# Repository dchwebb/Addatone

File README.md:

# Addatone

Overview
--------

Addatone is a Eurorack oscillator using additive synthesis. It is a two channel oscillator with channel one outputting fundamental and odd harmonics and channel two fundamental and even harmonics.

Each channel has potentiometer and CV control over the number of harmonics with higher harmonics progressively attenuated. In addition a 'Count' pot and CV input hard-limit the total number of audible harmonics. A warp control progressively detunes the odd harmonics up and even harmonics down.

Channel one has a mix switch which allows a mix of both channels to be output from channel one. Channel two has a multiply switch which allows a multiple of both channels to be output from channel two (ie a ring modulation effect).

The final controls are an octave potentiometer covering a five octave range and a fine tune control covering around an octave.

Architecture
------------

The core sound generator is an ICE40UP5K FPGA from Lattice. This is responsible for generating the harmonics, mixing/multiplying and then outputting to the DAC via I2S protocol.

The module also contains an STM32F446 microcontroller which holds the FPGA bitstream in internal flash memory; this is used to program the FPGA on start-up via SPI. In addition the STM32 is used as an ADC to digitise and scale all potentiometer and CV control data. This is periodically transferred to the FPGA via SPI. The STM32 is clocked from an external 12MHz crystal. This is also used to drive the FPGA clock via the STM32 MCO (Master Clock Output) peripheral.

The DAC is a Texas Instruments PCM5100APW, operating 2 channels at 16 bits, 48kHz. Two op-amps are used to scale input CV voltages and to amplify the DAC output to Eurorack levels (8V peak to peak).

FPGA
----

A look-up table in block RAM (Sine_LUT) holds 2048 16 bit samples containing a single cycle sine wave. Individual harmonics are generated by traversing the LUT at a speed relative to the harmonic frequency.

The SamplePos_RAM 256 x 16 bit look-up table holds the current Sine LUT position of each harmonic. This position is advanced according to the harmonic's frequency at each sample and the sine sample is scaled and added to an accumulator. The initial values of the sample position LUT are pre-calculated to minimise 'crest factor'. If each harmonic started at position 0 of a sine wave then peaks and troughs would coincide to create a wave with an amplitude greater than the dynamic range of the system.

A graphical javascript tool to visualise and calculate minimal crest factor sample positions is available here:
https://htmlpreview.github.io/?https://raw.githubusercontent.com/dchwebb/Addatone/master/SamplePosLUT/SineLUT.htm

The FPGA receives its control data from the ADCs processed in the STM32. These are periodically sent via SPI and decoded using a custom peripheral (ADC_SPI_In).

The DAC_I2S module is a custom peripheral used to dispatch the final sample values to the DAC via the I2S protocol.

The 12MHz clock received from the STM32 MCO is scaled to the ICE40's maximum clock frequency of 48MHz.

The ICE40 bitstream is developed in Lattice's Radiant IDE. Full source code here: https://github.com/dchwebb/Addatone/tree/master/Addatone_ICE40

STM32 Microcontroller
---------------------

The module includes an STM32F446 MCU that carries out various helper roles. The firmware was developed in STM's CubeIDE and available here: https://github.com/dchwebb/Addatone/tree/master/Addatone_STM32F446

The FPGA bitstream is stored in the MCU's flash memory and is programmed into the FPGA at startup using an STM32 SPI peripheral (see fpgaHandler::ProgramBitstream method). Once the FPGA is programmed the ADC data derived from external CV control and potentiometers is processed, scaled and transmitted in a periodic packet to the FPGA via SPI (see fpgaHandler::SendControls method).

Calibration
-----------

The 'calib' button allows the setting of the mid point of the fine tune and the spread of the tuning. To start calibration turn the Octave and Fine Tune knobs to their mid point position.

Press the Calib button. Changing the Fine Tune knob will alter the pitch. Turning the Octave knob clockwise will decrease the tuning spread, and vice versa.

When calibration is complete press the Calib button again. Turning the Fine Tune knob to the center position should set the correct pitch.

To erase the configured calibration hold the Calib button down when powering on the module.

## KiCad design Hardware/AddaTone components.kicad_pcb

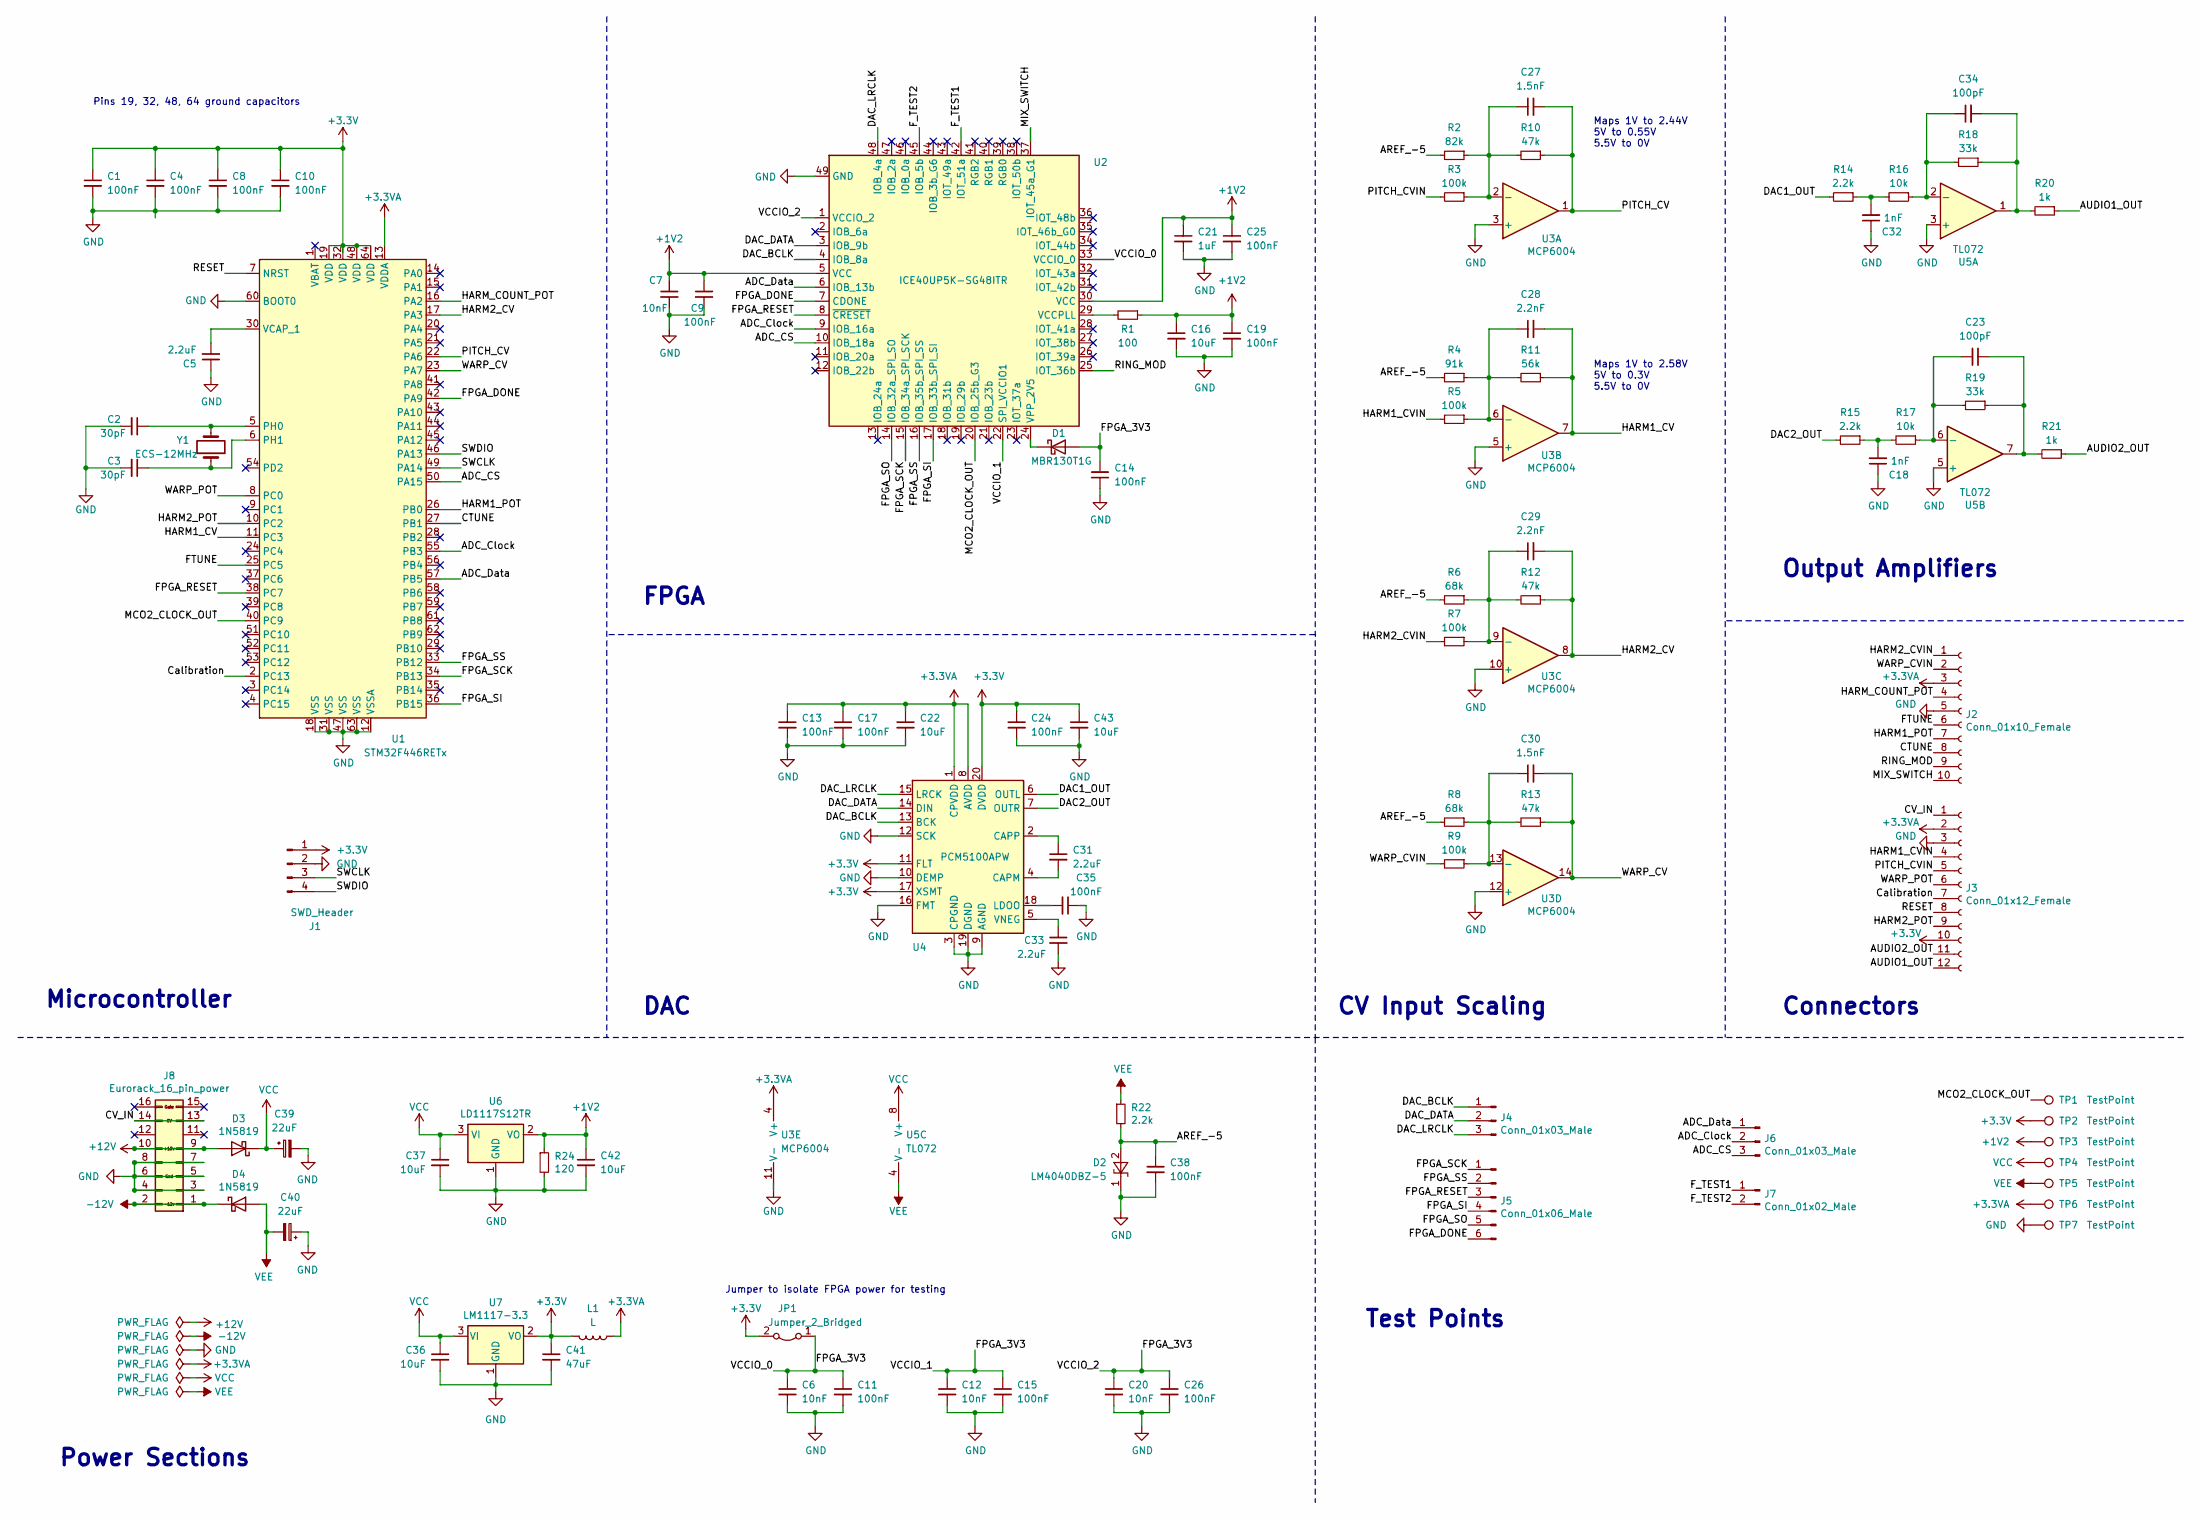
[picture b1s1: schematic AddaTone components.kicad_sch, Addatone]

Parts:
C1, C4, C9, C15, C35: 100nF; C_0603_1608Metric_Pad1.08x0.95mm_HandSolder
C2, C3: 30pF; C_0805_2012Metric_Pad1.18x1.45mm_HandSolder
C5, C31, C33: 2.2uF; C_0805_2012Metric_Pad1.18x1.45mm_HandSolder
C6, C7, C12, C20: 10nF; C_0805_2012Metric_Pad1.18x1.45mm_HandSolder
C8, C10, C11, C13, C14, C17, C19, C24, C25, C26, C38: 100nF; C_0805_2012Metric_Pad1.18x1.45mm_HandSolder
C16, C22, C43: 10uF; C_0805_2012Metric_Pad1.18x1.45mm_HandSolder
C18, C32: 1nF; C_0805_2012Metric_Pad1.18x1.45mm_HandSolder
C21: 1uF; C_0805_2012Metric_Pad1.18x1.45mm_HandSolder
C23, C34: 100pF; C_0805_2012Metric_Pad1.18x1.45mm_HandSolder
C27, C30: 1.5nF; C_0805_2012Metric_Pad1.18x1.45mm_HandSolder
C28, C29: 2.2nF; C_0805_2012Metric_Pad1.18x1.45mm_HandSolder
C36, C37, C42: 10uF; CP_Elec_3x5.3
C39, C40: 22uF; CP_Elec_5x5.3
C41: 47uF; CP_Elec_5x5.3
D1: MBR130T1G; D_SOD-123
D2: LM4040DBZ-5; SOT-23
D3, D4: 1N5819; D_SOD-123
J1: SWD_Header; SWD_header
J2: Conn_01x10_Female; PinSocket_1x10_P2.54mm_Vertical
J3: Conn_01x12_Female; PinSocket_1x12_P2.54mm_Vertical
J4, J6: Conn_01x03_Male; PinHeader_1x03_P2.54mm_Vertical
J5: Conn_01x06_Male; PinHeader_2x03_P2.54mm_Vertical
J7: Conn_01x02_Male; PinHeader_1x02_P2.54mm_Vertical
J8: Eurorack_16_pin_power; Eurorack_16_pin_header
JP1: Jumper_2_Bridged; SolderJumper-2_P1.3mm_Bridged_Pad1.0x1.5mm
L1: L; L_0805_2012Metric_Pad1.15x1.40mm_HandSolder
R1: 100; R_0805_2012Metric_Pad1.20x1.40mm_HandSolder
R2: 82k; R_0805_2012Metric_Pad1.20x1.40mm_HandSolder
R3, R5, R7, R9: 100k; R_0805_2012Metric_Pad1.20x1.40mm_HandSolder
R4: 91k; R_0805_2012Metric_Pad1.20x1.40mm_HandSolder
R6, R8: 68k; R_0805_2012Metric_Pad1.20x1.40mm_HandSolder
R10, R12, R13: 47k; R_0805_2012Metric_Pad1.20x1.40mm_HandSolder
R11: 56k; R_0805_2012Metric_Pad1.20x1.40mm_HandSolder
R14, R15, R22: 2.2k; R_0805_2012Metric_Pad1.20x1.40mm_HandSolder
R16, R17: 10k; R_0805_2012Metric_Pad1.20x1.40mm_HandSolder
R18, R19: 33k; R_0805_2012Metric_Pad1.20x1.40mm_HandSolder
R20, R21: 1k; R_0805_2012Metric_Pad1.20x1.40mm_HandSolder
R24: 120; R_0805_2012Metric_Pad1.20x1.40mm_HandSolder
TP1, TP2, TP3, TP4, TP5, TP6, TP7: TestPoint; TestPoint_THTPad_2.0x2.0mm_Drill1.0mm
U1: STM32F446RETx; LQFP-64_10x10mm_P0.5mm
U2: ICE40UP5K-SG48ITR; ICE40_QFN-48-1EP_7x7mm_Pitch0.5mm
U3: MCP6004; SOIC-14_3.9x8.7mm_P1.27mm
U4: PCM5100APW; SSOP-20_4.4x6.5mm_Pitch0.65mm_Round_Pads
U5: TL072; SOIC-8_3.9x4.9mm_P1.27mm
U6: LD1117S12TR; SOT-223
U7: LM1117-3.3; SOT-223
Y1: ECS-12MHz; Crystal_SMD_0603-2pin_6.0x3.5mm_HandSoldering

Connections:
+1V2: C7.1, C9.1, C16.1, C19.1, C21.1, C25.1, C42.1, R1.1, R24.1, TP3.1, U2.5 (VCC), U2.30 (VCC), U6.2 (VO)
+3.3VA: C13.1, C17.1, C22.1, J2.3, J3.2, L1.1, TP6.1, U1.13 (VDDA), U3.4 (V+), U4.1 (CPVDD), U4.8 (AVDD)
+3V3: C1.1, C4.1, C8.1, C10.1, C24.1, C41.1, C43.1, J1.1, J3.10, JP1.2 (B), L1.2, TP2.1, U1.19 (VDD), U1.32 (VDD), U1.48 (VDD), U1.64 (VDD), U4.11 (FLT), U4.17 (XSMT), U4.20 (DVDD), U7.2 (VO)
+12V: D3.2 (A), J8.9, J8.10
-12V: D4.1 (K), J8.1, J8.2
/ADC_CS: J6.3, U1.50 (PA15), U2.10 (IOB_18a)
/ADC_Clock: J6.2, U1.55 (PB3), U2.9 (IOB_16a)
/ADC_Data: J6.1, U1.57 (PB5), U2.6 (IOB_13b)
/AREF_-5: C38.1, D2.2 (A), R2.2, R4.2, R6.2, R8.2, R22.2
/AUDIO1_OUT: J3.12, R20.1
/AUDIO2_OUT: J3.11, R21.1
/CTUNE: J2.8, U1.27 (PB1)
/CV_IN: J3.1, J8.13, J8.14
/Calibration: J3.7, U1.2 (PC13)
/DAC1_OUT: R14.2, U4.6 (OUTL)
/DAC2_OUT: R15.2, U4.7 (OUTR)
/DAC_BCLK: J4.1, U2.4 (IOB_8a), U4.13 (BCK)
/DAC_DATA: J4.2, U2.3 (IOB_9b), U4.14 (DIN)
/DAC_LRCLK: J4.3, U2.48 (IOB_4a), U4.15 (LRCK)
/FPGA_3V3: C6.1, C11.1, C12.1, C14.2, C15.1, C20.1, C26.1, D1.2 (A), JP1.1 (A), U2.1 (VCCIO_2), U2.22 (SPI_VCCIO1), U2.33 (VCCIO_0)
/FPGA_DONE: J5.6, U1.42 (PA9), U2.7 (CDONE)
/FPGA_RESET: J5.3, U1.38 (PC7), U2.8 (~CRESET)
/FPGA_SCK: J5.1, U1.34 (PB13), U2.15 (IOB_34a_SPI_SCK)
/FPGA_SI: J5.4, U1.36 (PB15), U2.17 (IOB_33b_SPI_SI)
/FPGA_SO: J5.5, U2.14 (IOB_32a_SPI_SO)
/FPGA_SS: J5.2, U1.33 (PB12), U2.16 (IOB_35b_SPI_SS)
/FTUNE: J2.6, U1.25 (PC5)
/F_TEST1: J7.1, U2.42 (IOT_51a)
/F_TEST2: J7.2, U2.45 (IOB_5b)
/HARM1_CV: C28.2, R11.1, U1.11 (PC3), U3.7
/HARM1_CVIN: J3.4, R5.2
/HARM1_POT: J2.7, U1.26 (PB0)
/HARM2_CV: C29.2, R12.1, U1.17 (PA3), U3.8
/HARM2_CVIN: J2.1, R7.2
/HARM2_POT: J3.9, U1.10 (PC2)
/HARM_COUNT_POT: J2.4, U1.16 (PA2)
/MCO2_CLOCK_OUT: TP1.1, U1.40 (PC9), U2.20 (IOB_25b_G3)
/MIX_SWITCH: J2.10, U2.37 (IOT_45a_G1)
/PITCH_CV: C27.2, R10.1, U1.22 (PA6), U3.1
/PITCH_CVIN: J3.5, R3.2
/RESET: J3.8, U1.7 (NRST)
/RING_MOD: J2.9, U2.25 (IOT_36b)
/SWCLK: J1.3, U1.49 (PA14)
/SWDIO: J1.4, U1.46 (PA13)
/WARP_CV: C30.2, R13.1, U1.23 (PA7), U3.14
/WARP_CVIN: J2.2, R9.2
/WARP_POT: J3.6, U1.8 (PC0)
GND: C1.2, C2.2, C3.2, C4.2, C5.1, C6.2, C7.2, C8.2, C9.2, C10.2, C11.2, C12.2, C13.2, C14.1, C15.2, C16.2, C17.2, C18.1, C19.2, C20.2, C21.2, C22.2, C24.2, C25.2, C26.2, C32.1, C33.2, C35.1, C36.2, C37.2, C38.2, C39.2, C40.1, C41.2, C42.2, C43.2, D2.1 (K), J1.2, J2.5, J3.3, J8.3, J8.4, J8.5, J8.6, J8.7, J8.8, R24.2, TP7.1, U1.12 (VSSA), U1.18 (VSS), U1.31 (VSS), U1.47 (VSS), U1.60 (BOOT0), U1.63 (VSS), U2.49 (GND), U3.3 (+), U3.5 (+), U3.10 (+), U3.11 (V-), U3.12 (+), U4.3 (CPGND), U4.9 (AGND), U4.10 (DEMP), U4.12 (SCK), U4.16 (FMT), U4.19 (DGND), U5.3 (+), U5.5 (+), U6.1 (GND), U7.1 (GND)
unnamed: C18.2, R15.1, R17.2
unnamed: C23.2, R19.1, R21.2, U5.7
unnamed: C32.2, R14.1, R16.2
unnamed: C34.2, R18.1, R20.2, U5.1
unnamed: D1.1 (K), U2.24 (VPP_2V5)
unnamed: C2.1, U1.5 (PH0), Y1.2
unnamed: C3.1, U1.6 (PH1), Y1.1
unnamed: C5.2, U1.30 (VCAP_1)
unnamed: R1.2, U2.29 (VCCPLL)
unnamed: C27.1, R2.1, R3.1, R10.2, U3.2 (-)
unnamed: C28.1, R4.1, R5.1, R11.2, U3.6 (-)
unnamed: C29.1, R6.1, R7.1, R12.2, U3.9 (-)
unnamed: C30.1, R8.1, R9.1, R13.2, U3.13 (-)
unnamed: C31.2, U4.4 (CAPM)
unnamed: C31.1, U4.2 (CAPP)
unnamed: C35.2, U4.18 (LDOO)
unnamed: C33.1, U4.5 (VNEG)
unnamed: C34.1, R16.1, R18.2, U5.2 (-)
unnamed: C23.1, R17.1, R19.2, U5.6 (-)
VCC: C36.1, C37.1, C39.1, D3.1 (K), TP4.1, U5.8 (V+), U6.3 (VI), U7.3 (VI)
VEE: C40.2, D4.2 (A), R22.1, TP5.1, U5.4 (V-)

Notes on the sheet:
Pins 19, 32, 48, 64 ground capacitors
Test Points
Power Sections
DAC
Jumper to isolate FPGA power for testing
Output Amplifiers
Microcontroller
Maps 1V to 2.44V 5V to 0.55V 5.5V to 0V
Maps 1V to 2.58V 5V to 0.3V 5.5V to 0V
CV Input Scaling
Connectors
FPGA

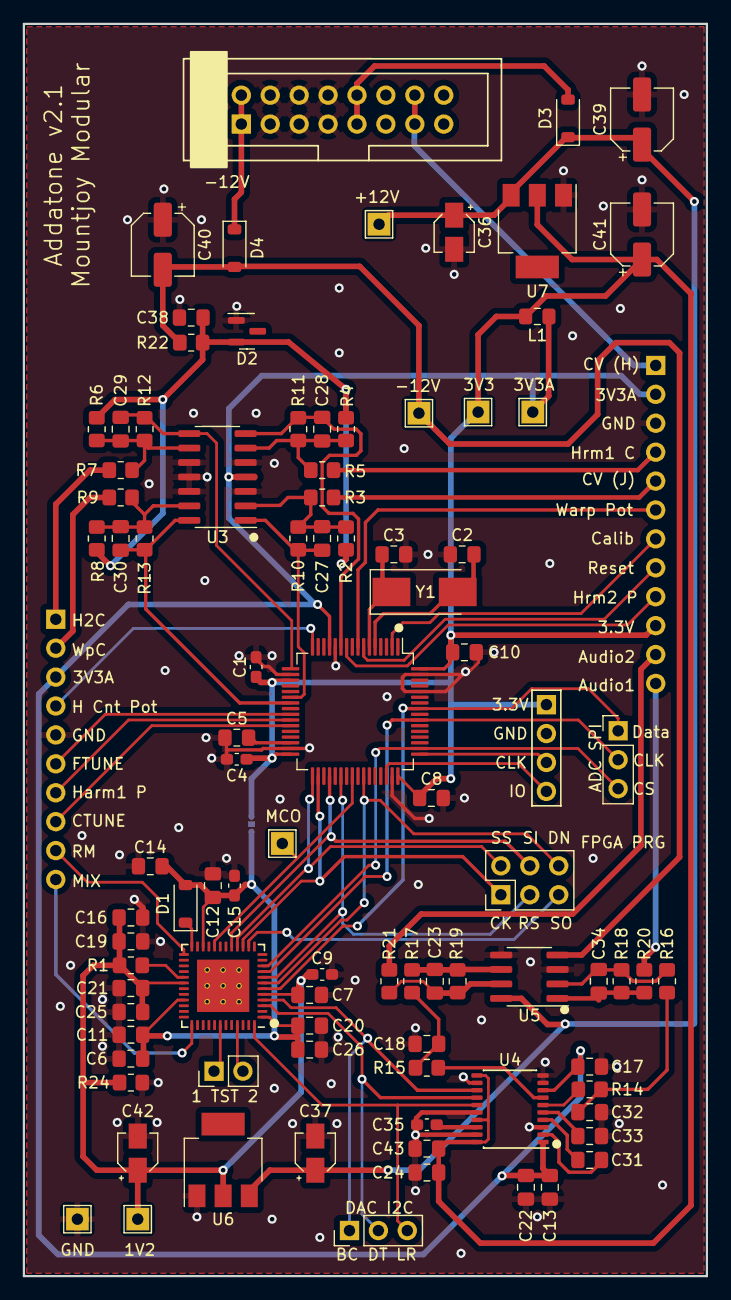
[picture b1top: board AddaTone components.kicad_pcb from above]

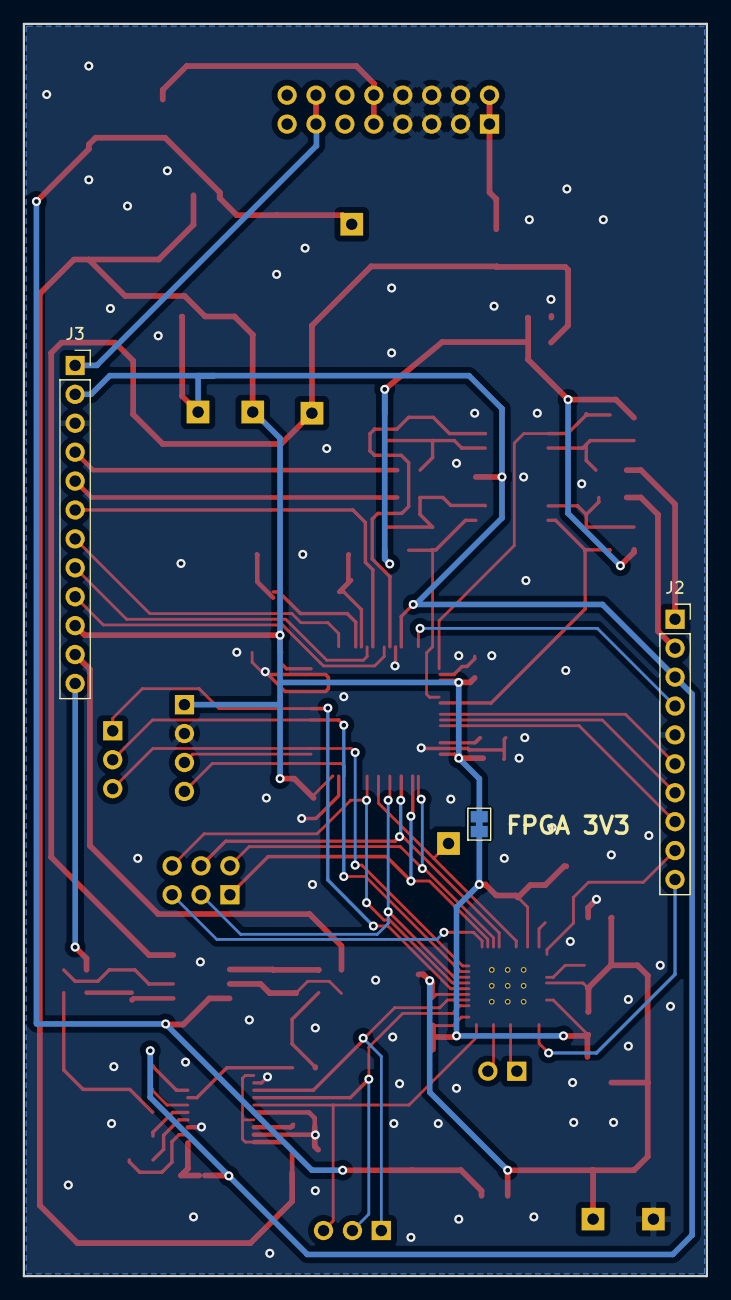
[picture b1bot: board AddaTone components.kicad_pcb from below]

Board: 2 copper layers, 60.0 x 110.0 mm, 95 parts (3 on the bottom side), 69 nets.

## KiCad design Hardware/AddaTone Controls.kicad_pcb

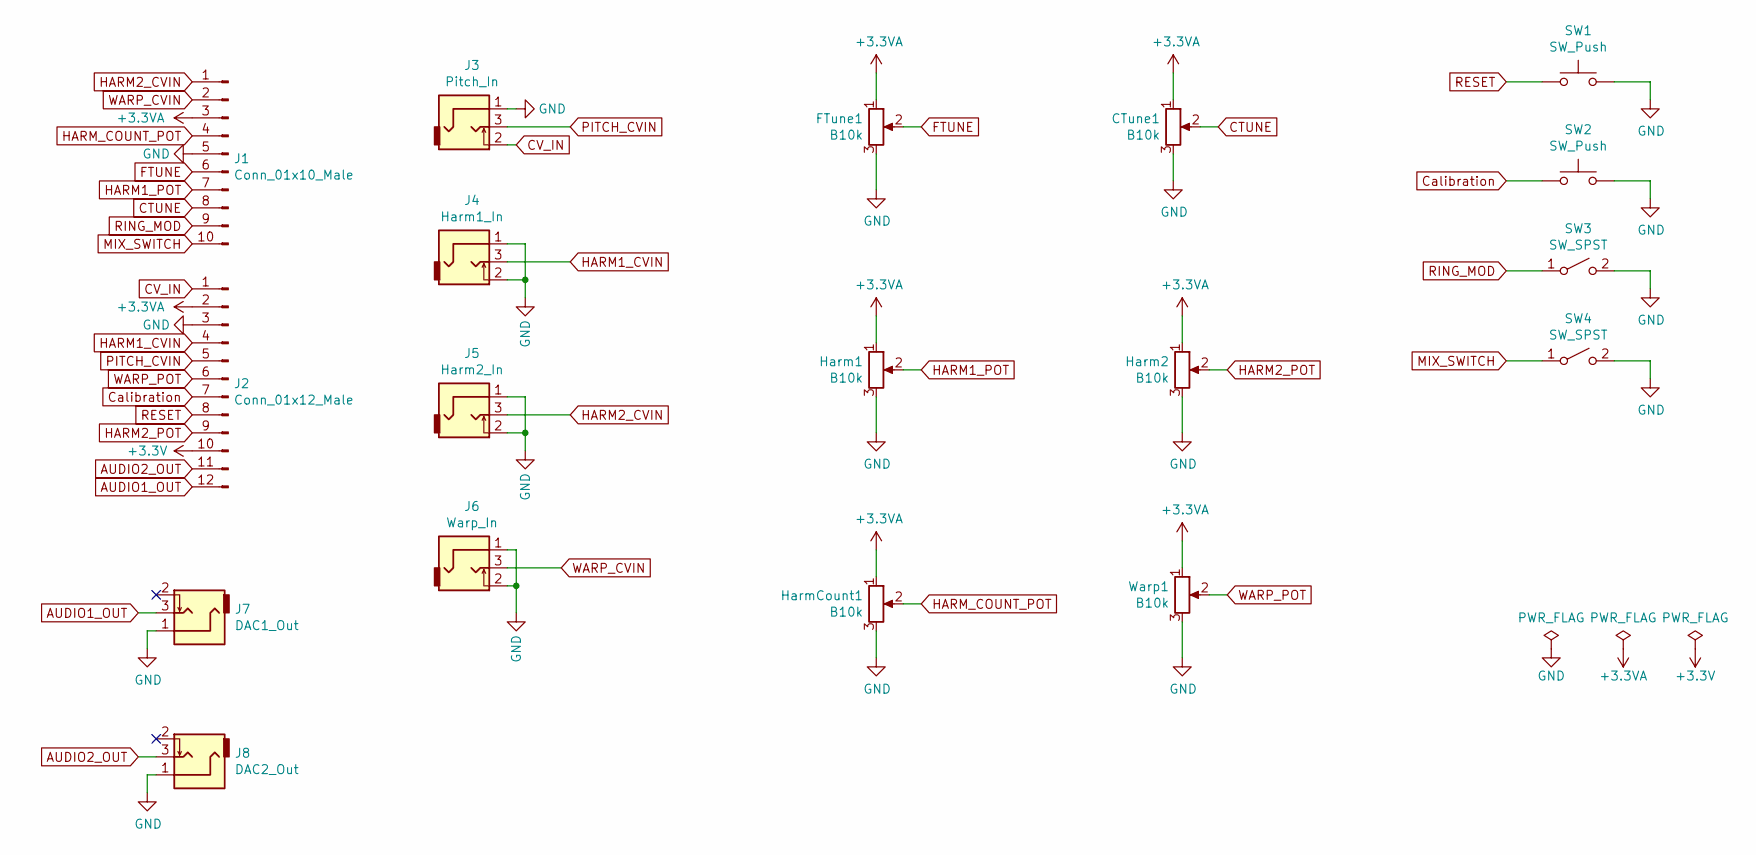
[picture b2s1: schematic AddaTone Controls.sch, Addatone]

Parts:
CTune1: B10k; Alpha_9mm_Potentiometer
FTune1: B10k; Alpha_9mm_Potentiometer
Harm1, Harm2: B10k; Alpha_9mm_Potentiometer
HarmCount1: B10k; Alpha_9mm_Potentiometer
J1: Conn_01x10_Male; Pin_Header_Straight_1x10_Pitch2.54mm
J2: Conn_01x12_Male; Pin_Header_Straight_1x12_Pitch2.54mm
J3: Pitch_In; THONKICONN_hole
J4: Harm1_In; THONKICONN_hole
J5: Harm2_In; THONKICONN_hole
J6: Warp_In; THONKICONN_hole
J7: DAC1_Out; THONKICONN_hole
J8: DAC2_Out; THONKICONN_hole
SW1, SW2: SW_Push; SW_PUSH_6mm
SW3, SW4: SW_SPST; SPDTSubMiniature
Warp1: B10k; Alpha_9mm_Potentiometer

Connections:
+3.3VA: CTune1.1, FTune1.1, Harm1.1, Harm2.1, HarmCount1.1, J1.3, J2.2, Warp1.1
+3V3: J2.10
AUDIO1_OUT: J2.12, J7.3
AUDIO2_OUT: J2.11, J8.3
CTUNE: CTune1.2, J1.8
CV_IN: J2.1, J3.2
Calibration: J2.7, SW2.1
FTUNE: FTune1.2, J1.6
GND: CTune1.3, FTune1.3, Harm1.3, Harm2.3, HarmCount1.3, J1.5, J2.3, J3.1, J4.1, J4.2, J5.1, J5.2, J6.1, J6.2, J7.1, J8.1, SW1.2, SW2.2, SW3.2 (B), SW4.2 (B), Warp1.3
HARM1_CVIN: J2.4, J4.3
HARM1_POT: Harm1.2, J1.7
HARM2_CVIN: J1.1, J5.3
HARM2_POT: Harm2.2, J2.9
HARM_COUNT_POT: HarmCount1.2, J1.4
MIX_SWITCH: J1.10, SW4.1 (A)
PITCH_CVIN: J2.5, J3.3
RESET: J2.8, SW1.1
RING_MOD: J1.9, SW3.1 (A)
WARP_CVIN: J1.2, J6.3
WARP_POT: J2.6, Warp1.2

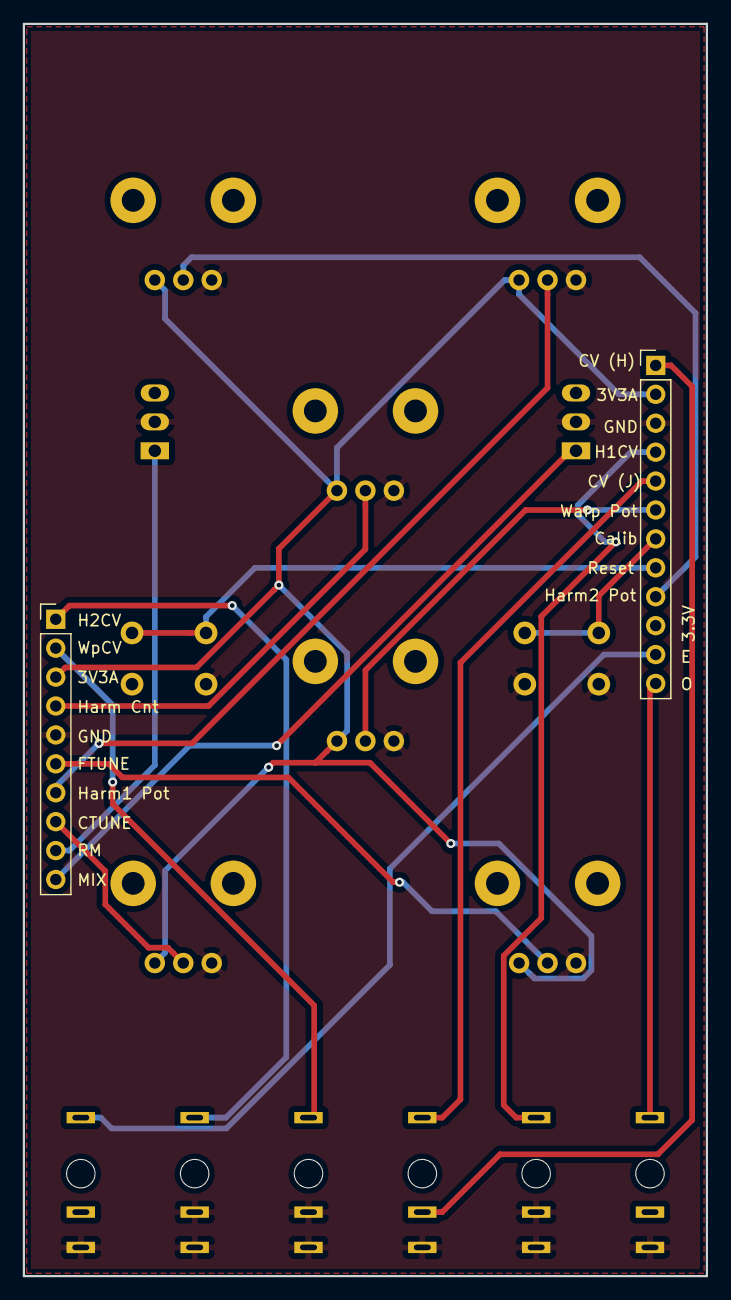
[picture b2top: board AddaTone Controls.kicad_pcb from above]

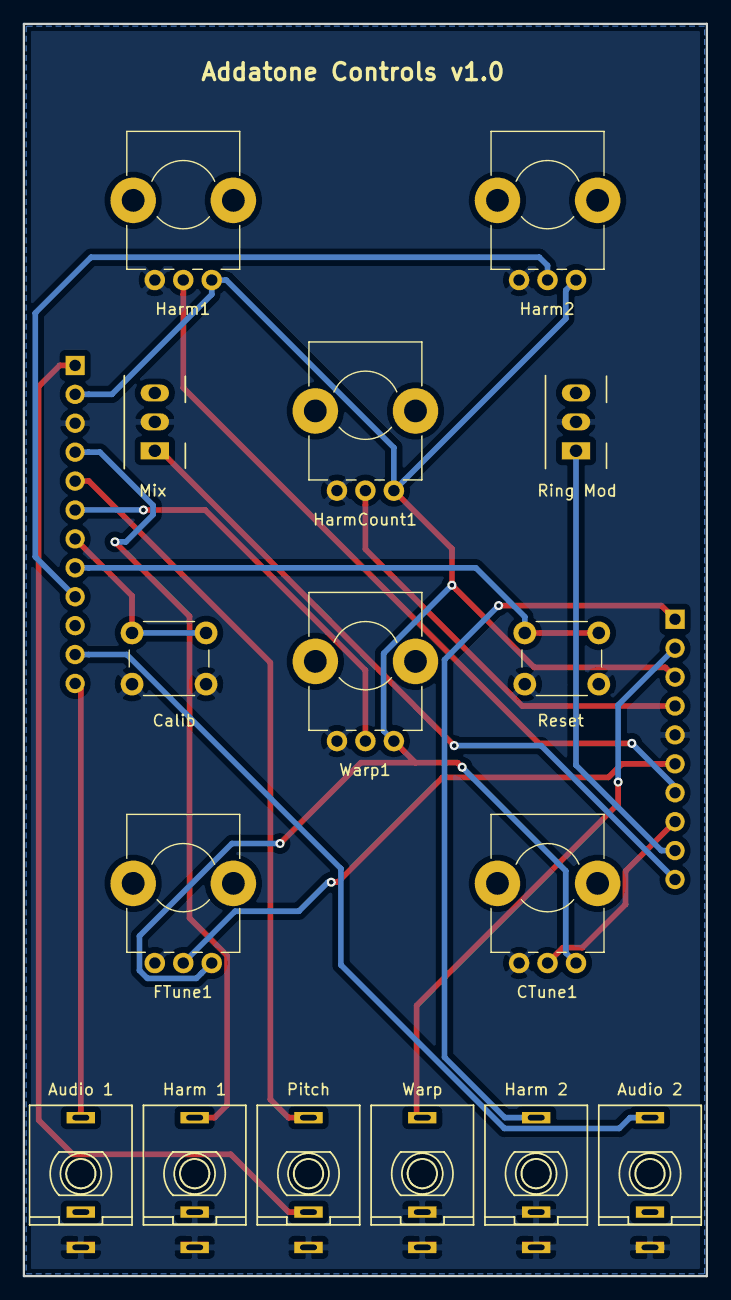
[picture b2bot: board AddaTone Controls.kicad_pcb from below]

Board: 2 copper layers, 60.0 x 110.0 mm, 18 parts (16 on the bottom side), 19 nets.

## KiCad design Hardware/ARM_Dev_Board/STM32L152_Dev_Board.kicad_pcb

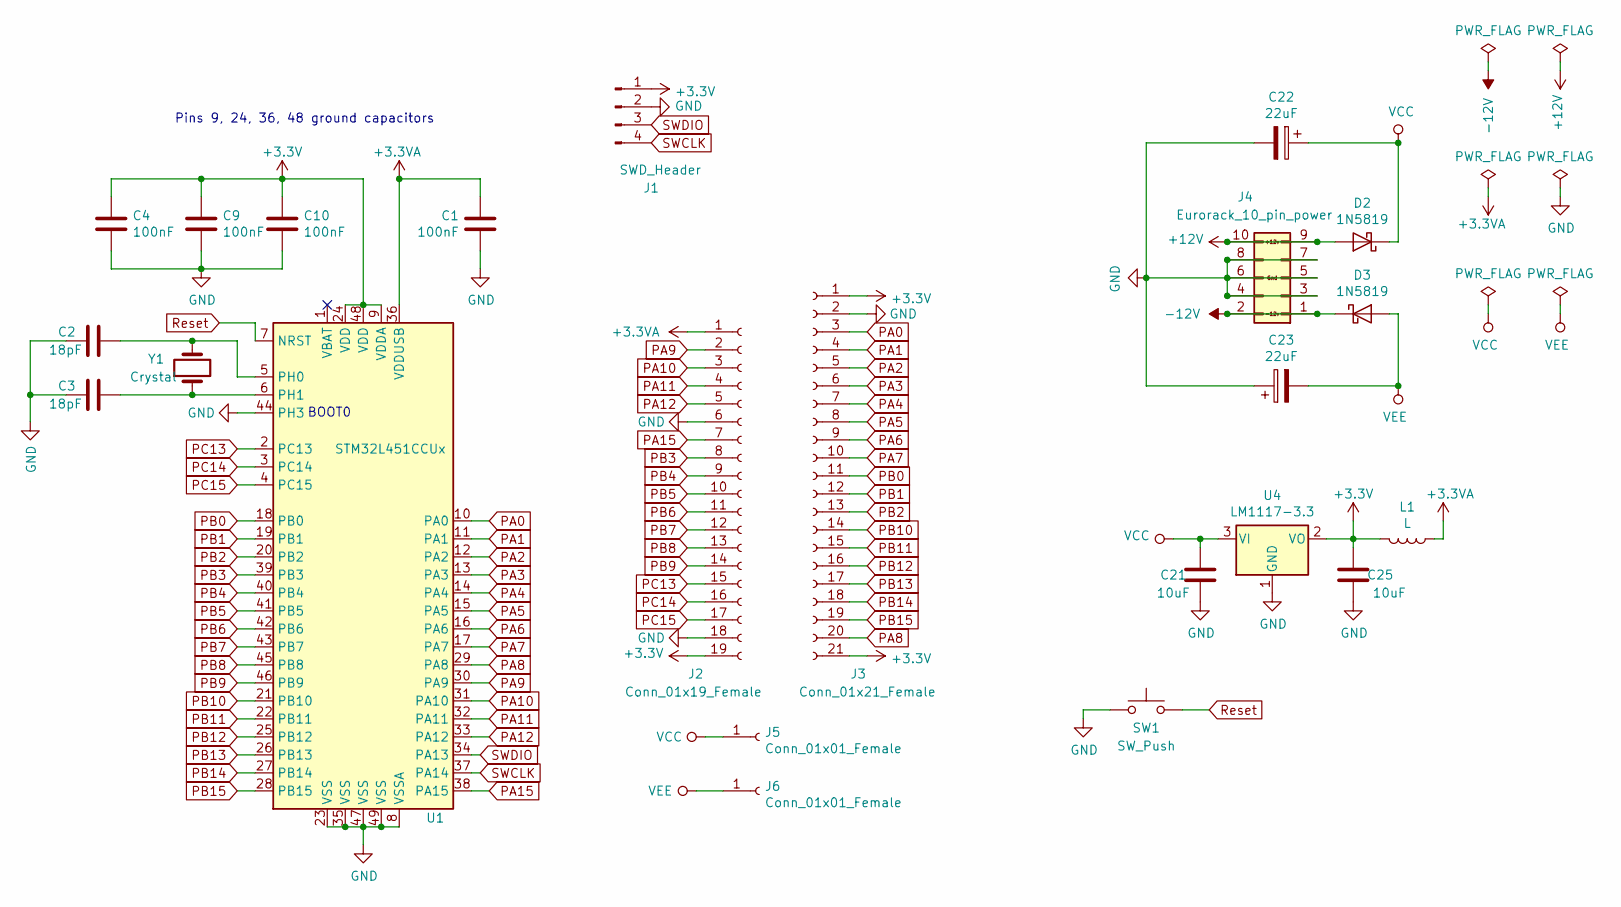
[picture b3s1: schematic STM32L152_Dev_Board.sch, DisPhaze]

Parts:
C1, C4, C9, C10: 100nF; C_0805_HandSoldering
C2, C3: 18pF; C_0805_HandSoldering
C21, C25: 10uF; CP_Elec_3x5.3
C22, C23: 22uF; CP_Elec_4x5.8_Big_pad
D2, D3: 1N5819; D_SOD-123
J1: SWD_Header; SWD_header
J2: Conn_01x19_Female; Pin_Header_Straight_1x19_Pitch2.54mm
J3: Conn_01x21_Female; Pin_Header_Straight_1x21_Pitch2.54mm
J4: Eurorack_10_pin_power; Pin_Header_Straight_2x05_Pitch2.54mm
J5, J6: Conn_01x01_Female; Pin_Header_Straight_1x01_Pitch2.54mm
L1: L; R_0805_HandSoldering
SW1: SW_Push; SW_SPST_EVPBF
U1: STM32L451CCUx; ICE40_QFN-48-1EP_7x7mm_Pitch0.5mm
U4: LM1117-3.3; SOT-223
Y1: Crystal; Crystal_SMD_0603-2pin_6.0x3.5mm_HandSoldering

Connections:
+3.3VA: C1.1, J2.1, L1.1, U1.36 (VDDUSB)
+3V3: C4.1, C9.1, C10.1, C25.1, J1.1, J2.19, J3.1, J3.21, L1.2, U1.9 (VDDA), U1.24 (VDD), U1.48 (VDD), U4.2 (VO)
+12V: D2.2 (A), J4.9, J4.10
-12V: D3.1 (K), J4.1, J4.2
GND: C1.2, C2.2, C3.2, C4.2, C9.2, C10.2, C21.2, C22.2, C23.1, C25.2, J1.2, J2.6, J2.18, J3.2, J4.3, J4.4, J4.5, J4.6, J4.7, J4.8, SW1.1, U1.8 (VSSA), U1.23 (VSS), U1.35 (VSS), U1.44 (PH3), U1.47 (VSS), U1.49 (VSS), U4.1 (GND)
unnamed: C2.1, U1.5 (PH0), Y1.2
unnamed: C3.1, U1.6 (PH1), Y1.1
PA0: J3.3, U1.10 (PA0)
PA1: J3.4, U1.11 (PA1)
PA2: J3.5, U1.12 (PA2)
PA3: J3.6, U1.13 (PA3)
PA4: J3.7, U1.14 (PA4)
PA5: J3.8, U1.15 (PA5)
PA6: J3.9, U1.16 (PA6)
PA7: J3.10, U1.17 (PA7)
PA8: J3.20, U1.29 (PA8)
PA9: J2.2, U1.30 (PA9)
PA10: J2.3, U1.31 (PA10)
PA11: J2.4, U1.32 (PA11)
PA12: J2.5, U1.33 (PA12)
PA15: J2.7, U1.38 (PA15)
PB0: J3.11, U1.18 (PB0)
PB1: J3.12, U1.19 (PB1)
PB2: J3.13, U1.20 (PB2)
PB3: J2.8, U1.39 (PB3)
PB4: J2.9, U1.40 (PB4)
PB5: J2.10, U1.41 (PB5)
PB6: J2.11, U1.42 (PB6)
PB7: J2.12, U1.43 (PB7)
PB8: J2.13, U1.45 (PB8)
PB9: J2.14, U1.46 (PB9)
PB10: J3.14, U1.21 (PB10)
PB11: J3.15, U1.22 (PB11)
PB12: J3.16, U1.25 (PB12)
PB13: J3.17, U1.26 (PB13)
PB14: J3.18, U1.27 (PB14)
PB15: J3.19, U1.28 (PB15)
PC13: J2.15, U1.2 (PC13)
PC14: J2.16, U1.3 (PC14)
PC15: J2.17, U1.4 (PC15)
Reset: SW1.2, U1.7 (NRST)
SWCLK: J1.4, U1.37 (PA14)
SWDIO: J1.3, U1.34 (PA13)
VCC: C21.1, C22.1, D2.1 (K), J5.1, U4.3 (VI)
VEE: C23.2, D3.2 (A), J6.1

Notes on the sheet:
Pins 9, 24, 36, 48 ground capacitors
BOOT0

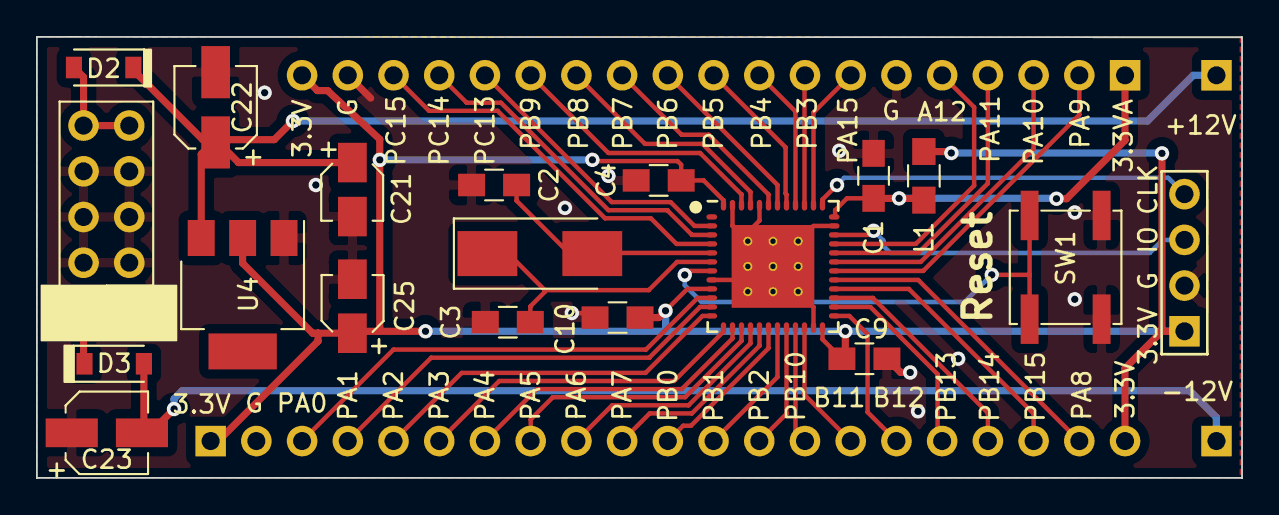
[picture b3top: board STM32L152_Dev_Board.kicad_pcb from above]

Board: 2 copper layers, 67.0 x 24.5 mm, 23 parts (0 on the bottom side), 45 nets.
